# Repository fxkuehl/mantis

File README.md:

# Mantis hex ergo keyboard — Development branch

>

This is the development branch of Mantis. It's taking me way longer than expected to finish version 1.0 for various reasons—including my day job, other hobbies, some pretty ambitious design goals, and having too much fun making the renders look pretty. But I am getting closer to the finish line, so it's a good time to share an update in January 2026.

## What's unchanged since v0.3

>

The basic recipe is still the same:

* Compact unibody keyboard with 40 sculpted hexagonal keys
* Simulated key wells using two layers of PCBs and rotated switches
* 30° hand rotation
* 15° tenting
* Choc switches
* Support for per-key RGB LEDs

## What's new in v1.0

>

These are mostly the features that I wanted v1.0 to have when I started working on it in November 2024:

* Integrated trackball or trackpad
* 3D-printed, fully enclosed case hiding switches
* Gasket mounted structure
* New saddle-shaped key cap profile
* Choc v1 and v2 switch compatibility
* Hot-swap
* Designed for easier assembly
* Support for wireless builds with nice!nano
* Support for wired builds with ProMicro-RP2040
* Support for nice!view display

Only the nice!view display option was a later addition as wireless support became a higher priority for me and I realized that RGB LEDs don't work well with small batteries.

## Details and trade-offs

I figured the trackball would be harder to design for than a cirque trackpad, so I started with the trackball design. Once I got down to the nuts and bolts, these were some of the decisions and trade-offs that emerged:

* Trackball: 34mm, static bearings, PMW3610 sensor
    - ambidextrous
    - placement and sensor angle work best for thumb use
    - low power sensor, suitable for wireless builds
    - unfortunately not supported by QMK, but ZMK also supports wired RP2040 controllers
* Losing two thumb keys to make room for the trackball
* Adding two pinky keys to maintain number of keys, provide more layout flexibility
* Gasket-mounted structure allows 1mm vertical movement before bottoming out
* Four 1mm foam or cork layers for sound dampening
* Enclosed case adds minimal bulk with 2.5mm wall thickness and tight tolerances
    - case adds only about 1.5mm total width and depth compared to v0.3
    - extra pinky keys add another 21.5mm total width
* Low-profile design: 2mm lower than v0.3, including the trackball, 6mm lower excluding trackball
    - counter-sunk screws
    - recessed feet
    - internal recesses in base plate and mezzanine for PCB components and pins
    - thinner PCBs and switch plates (1.2mm)
    - 60° angled sensor mount and opening in case bottom enable low trackball position
* Internal use of VIK connectors/cables/signaling (ready for future version with Cirque trackpad)
    - Custom sensor-board is not mechanically VIK-compatible due to space constraints
    - Using identical 12-pin FFC cables for VIK connection and upper keyboard-PCB connection
* PCB configuration through solder jumpers
    - not enough controller pins to support all VIK features + display + LEDs all at once
    - support for cirque trackpads (without VIK module) requires disconnecting VIK 5V and LED pins
    - power source selection for LEDs depending on the controller
* Intended for automated PCB-assembly
    - no manual SMD soldering required (hand-soldering FFC connectors would be a pain)
    - all SMD components placed on the bottom of the PCBs
    - still requires manual soldering of jumpers and through-hole components
* Easy controller socketing with standard pin-headers
* Battery compartment and connector
    - using common JST-PH 2mm-pitch connector
    - accessible without disassembly other than removing the base plate
    - enough room for 501240, 501235, 401230 or similar LiPo batteries
    - 100-200mAh should be good for several weeks on a charge
* Attempting crude ESD protection with a ferrite bead between ground plane and controller GND pins
    - proper ESD would involve a [Unified Daughterboard](https://unified-daughterboard.github.io/#/) and integrated controller, but I'm not ready to make that jump in v1.0

## What's done

>

Over the last year and 2 months I went through more than 140 revisions on this Git branch to get to this point:

* Closed most open design and fit issues
* Ergogen design of all the PCB, plate and foam outlines and PCB templates
* Parametric OpenSCAD model of the case for gasket-mounted trackball version
* Parametric OpenSCAD models of saddle-shaped key cap profile with Choc v1 and v2 stems
* Main PCB schematic and routing complete

## What's left to do

If I can check off each of the following TODO items in a weekend, I'll have the first working prototype ready by the spring equinox. This estimate is on the optimistic side, given my track record. But if all works without major setbacks, I expect to publish the complete design and a build guide some time this spring.

High-level TODO-list:

* Upper PCB schematic and routing
* Fix-up the sensor board with updated outline and schematic
* Experiment with panelization and V-cuts to make multi-PCB+plate production easier/cheaper
* Create the PCB production files, order PCBs and plates
* Find some local 3D-printing/laser cutting services or maker spaces to make the case and foam/cork layers
* Order all the additional parts
* Build a prototype or two
* Learn ZMK and create the firmware
* Pray that everything fits and works as designed

## What's next

While the gasket-mounted trackball version is meant to be my ideal home or office keyboard, I want to make the perfect on-the-go or travel keyboard next. The PCBs are already designed to support this, so it should only be a matter of a modified case design and parameters as well as a different firmware build:

* Switch plates integrated into the case
    - more sturdy
    - easier assembly
    - slightly lower without the gaskets
* Cirque trackpad
    - biggest size I can fit is probably 35mm
    - mouse buttons integrated into the case
* Low-profile with shallower key-wells
    - tenting angle lowered to 10° (less rise between main and upper PCB/plate)
    - less-tilted key caps
    - aiming for about 25-26mm total height

>

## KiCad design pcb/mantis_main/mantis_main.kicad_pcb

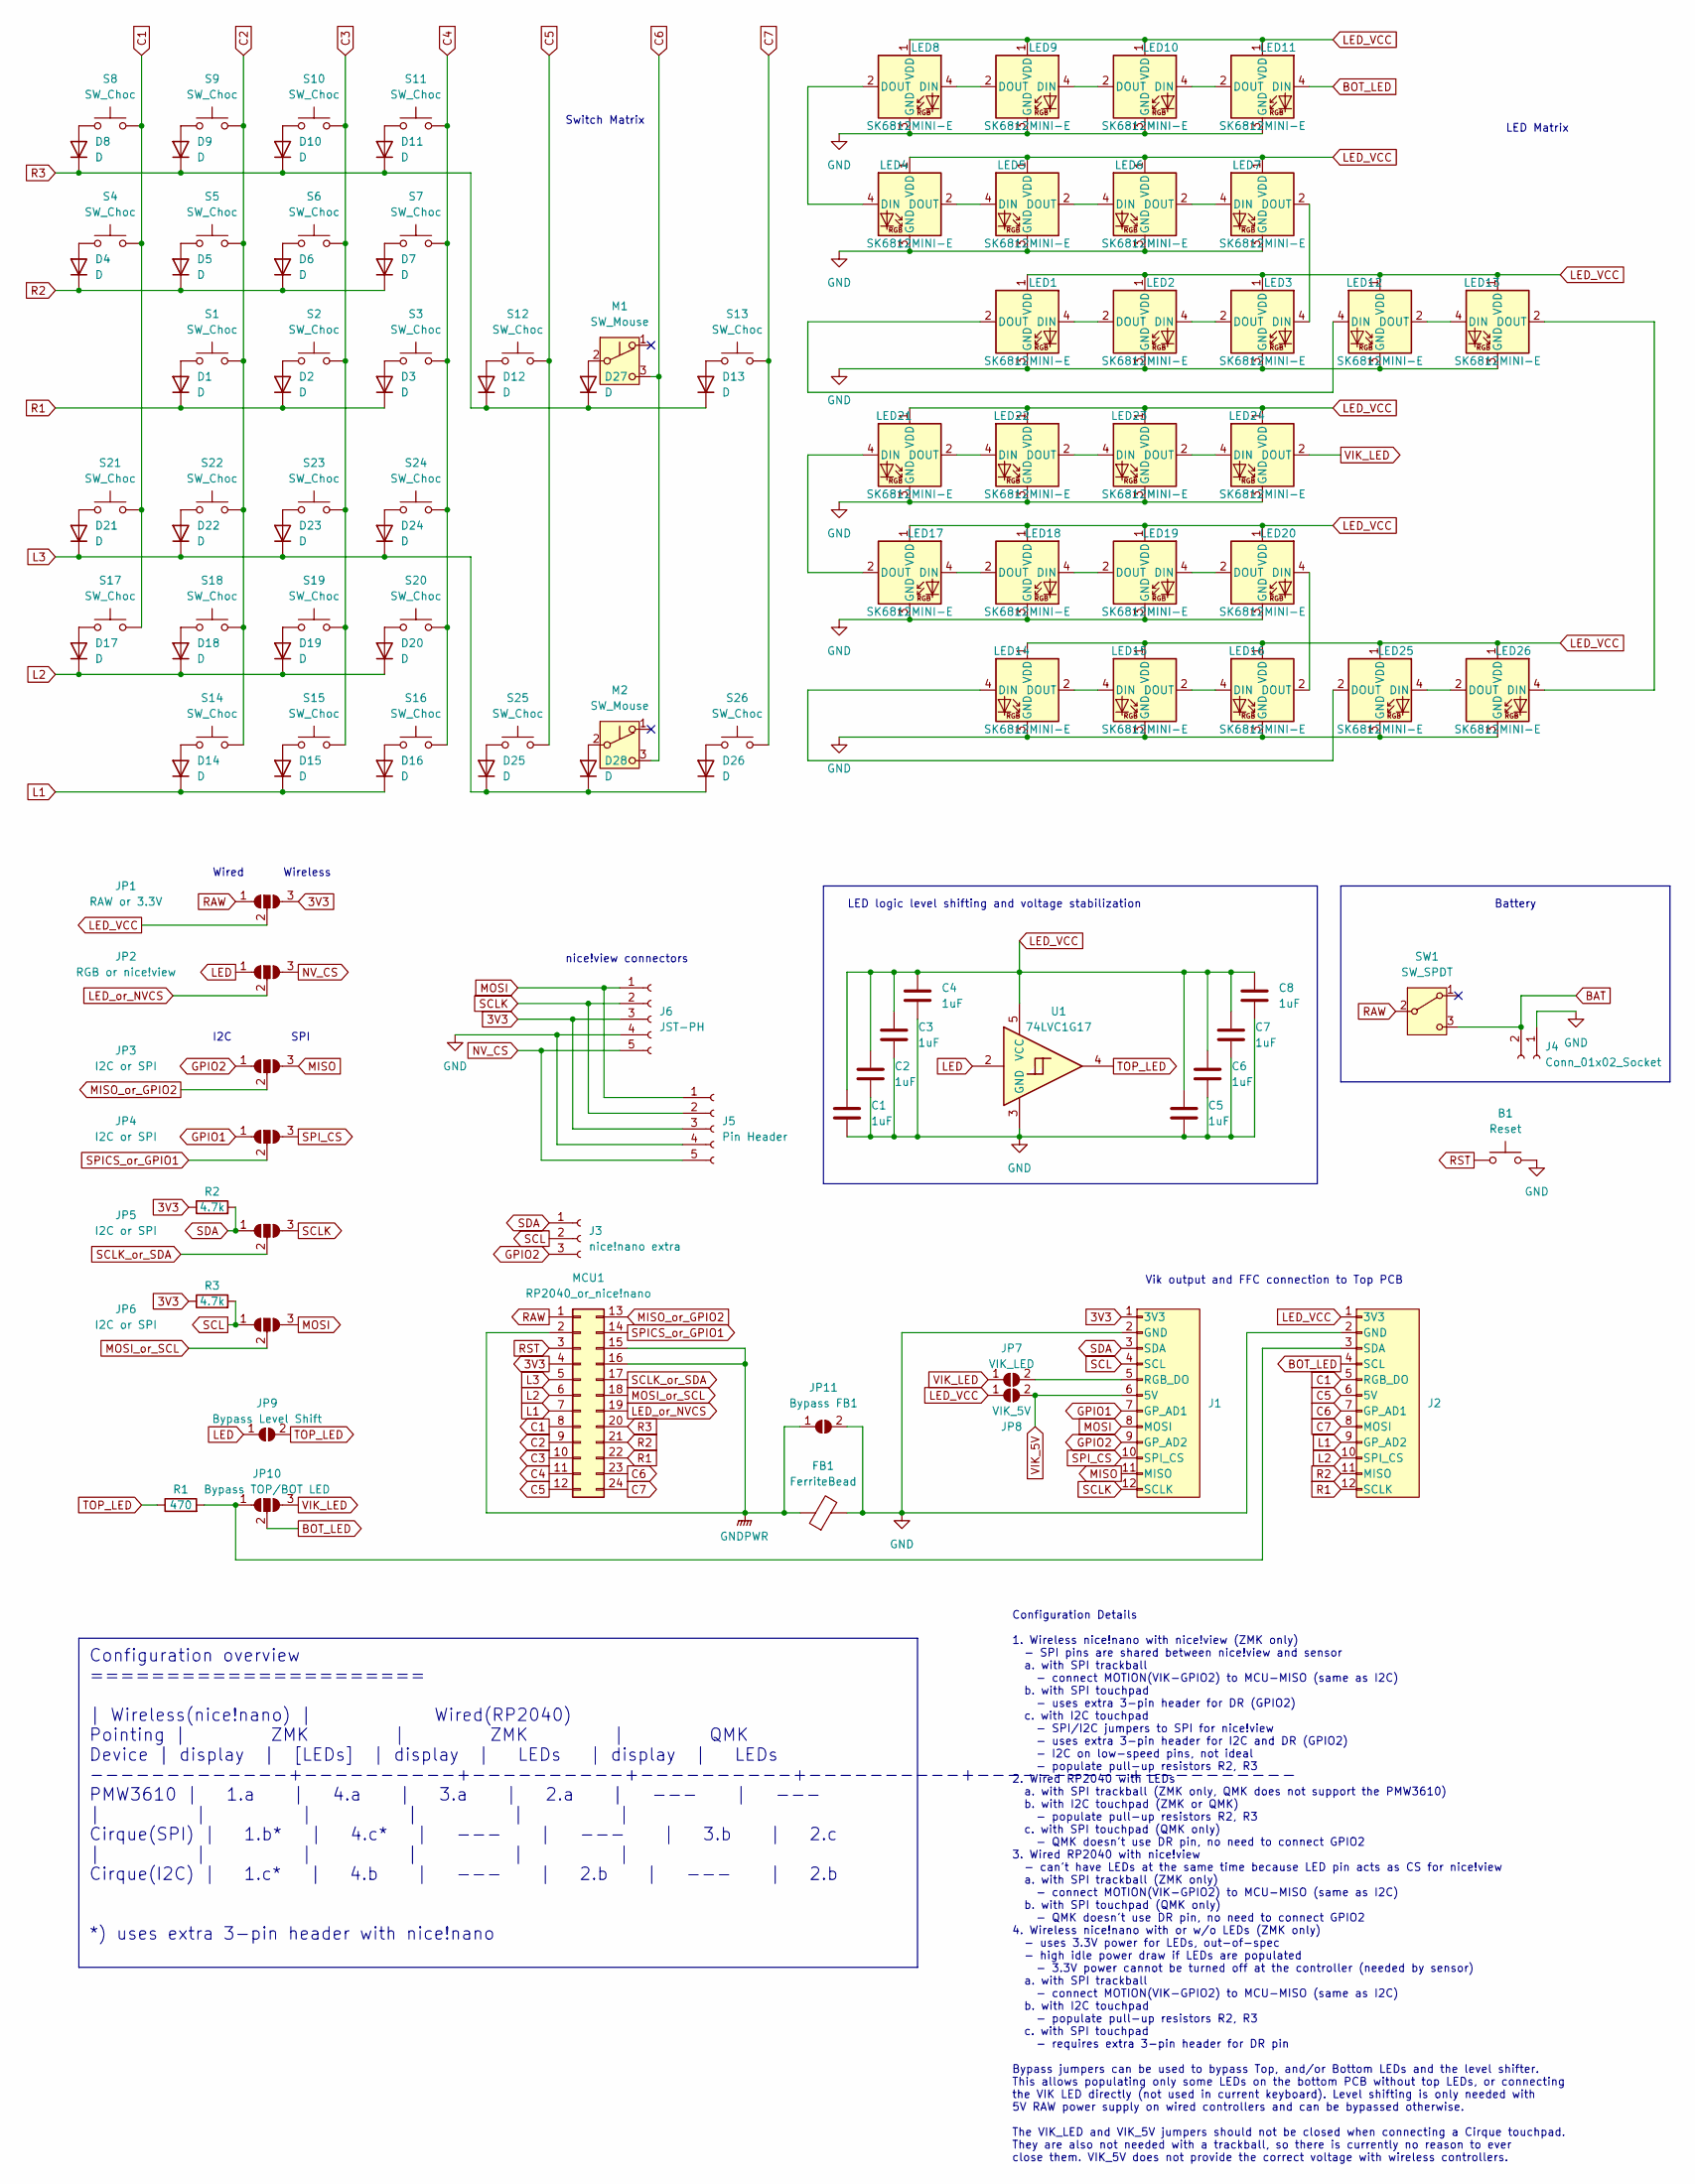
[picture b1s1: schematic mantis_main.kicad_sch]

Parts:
B1: Reset; SW_SPST_SKQG_WithoutStem
C1, C2, C3, C4, C5, C6, C7, C8: 1uF; C_0603_1608Metric
D1, D2, D3, D4, D5, D6, D7, D8, D9, D10, D11, D12, D13, D14, D15, D16, D17, D18, D19, D20, D21, D22, D23, D24, D25, D26, D27, D28: D; D_SOD-123
FB1: FerriteBead; C_0805_2012Metric
J1, J2: vik-keyboard-connector-horizontal
J3: nice!nano extra; PinSocket_1x03_P2.54mm_Vertical
J4: Conn_01x02_Socket; JST_PH_S2B-PH-K_1x02_P2.00mm_Horizontal
J5: Pin Header; PinSocket_1x05_P2.54mm_Vertical
J6: JST-PH; JST_PH_S5B-PH-K_1x05_P2.00mm_Horizontal
JP1: RAW or 3.3V; SolderJumper-3_P1.3mm_Open_RoundedPad1.0x1.5mm
JP2: RGB or nice!view; SolderJumper-3_P1.3mm_Open_RoundedPad1.0x1.5mm
JP3, JP4, JP5, JP6: I2C or SPI; SolderJumper-3_P1.3mm_Open_RoundedPad1.0x1.5mm
JP7: VIK_LED; SolderJumper-2_P1.3mm_Open_RoundedPad1.0x1.5mm
JP8: VIK_5V; SolderJumper-2_P1.3mm_Open_RoundedPad1.0x1.5mm
JP9: Bypass Level Shift; SolderJumper-2_P1.3mm_Open_RoundedPad1.0x1.5mm
JP10: Bypass TOP/BOT LED; SolderJumper-3_P1.3mm_Open_RoundedPad1.0x1.5mm
JP11: Bypass FB1; SolderJumper-2_P1.3mm_Open_RoundedPad1.0x1.5mm
LED1, LED2, LED3, LED4, LED5, LED6, LED7, LED8, LED9, LED10, LED11, LED12, LED13, LED14, LED15, LED16, LED17, LED18, LED19, LED20, LED21, LED22, LED23, LED24, LED25, LED26: SK6812MINI-E; SK6812_MINI-E-back
M1, M2: SW_Mouse; D2F
MCU1: RP2040_or_nice!nano; ProMicro-back
R1: 470; R_0603_1608Metric
R2, R3: 4.7k; R_0603_1608Metric
S1, S2, S3, S4, S5, S6, S7, S8, S9, S10, S11, S12, S13, S14, S15, S16, S17, S18, S19, S20, S21, S22, S23, S24, S25, S26: SW_Choc; PG1350-hotswap
SW1: SW_SPDT; SW_SPDT_PCM12
U1: 74LVC1G17; SOT-353_SC-70-5

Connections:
3V3: J1.1 (3V3), J5.3, J6.3, JP1.3 (B), MCU1.4, R2.1, R3.1
BAT: J4.2, SW1.3 (C)
BOT_LED: J2.4 (SCL), JP10.2 (C), LED11.4 (DIN)
C1: J2.5 (RGB_DO), MCU1.8, S4.2, S8.2, S17.2, S21.2
C2: MCU1.9, S1.2, S5.2, S9.2, S14.2, S18.2, S22.2
C3: MCU1.10, S2.2, S6.2, S10.2, S15.2, S19.2, S23.2
C4: MCU1.11, S3.2, S7.2, S11.2, S16.2, S20.2, S24.2
C5: J2.6 (5V), MCU1.12, S12.2, S25.2
C6: J2.7 (GP_AD1), M1.3 (C), M2.3 (C), MCU1.23
C7: J2.8 (MOSI), MCU1.24, S13.2, S26.2
GND: B1.2, C1.2, C2.2, C3.2, C4.2, C5.2, C6.2, C7.2, C8.2, FB1.2, J1.2 (GND), J2.2 (GND), J4.1, J5.4, J6.4, JP11.2 (B), LED1.3 (GND), LED2.3 (GND), LED3.3 (GND), LED4.3 (GND), LED5.3 (GND), LED6.3 (GND), LED7.3 (GND), LED8.3 (GND), LED9.3 (GND), LED10.3 (GND), LED11.3 (GND), LED12.3 (GND), LED13.3 (GND), LED14.3 (GND), LED15.3 (GND), LED16.3 (GND), LED17.3 (GND), LED18.3 (GND), LED19.3 (GND), LED20.3 (GND), LED21.3 (GND), LED22.3 (GND), LED23.3 (GND), LED24.3 (GND), LED25.3 (GND), LED26.3 (GND), U1.3 (GND)
GNDPWR: FB1.1, JP11.1 (A), MCU1.2, MCU1.15, MCU1.16
GPIO1: J1.7 (GP_AD1), JP4.1 (A)
GPIO2: J1.9 (GP_AD2), J3.3, JP3.1 (A)
L1: D14.1 (K), D15.1 (K), D16.1 (K), J2.9 (GP_AD2), MCU1.7
L2: D17.1 (K), D18.1 (K), D19.1 (K), D20.1 (K), J2.10 (SPI_CS), MCU1.6
L3: D21.1 (K), D22.1 (K), D23.1 (K), D24.1 (K), D25.1 (K), D26.1 (K), D28.1 (K), MCU1.5
LED: JP2.1 (A), JP9.1 (A), U1.2
LED_VCC: C1.1, C2.1, C3.1, C4.1, C5.1, C6.1, C7.1, C8.1, J2.1 (3V3), JP1.2 (C), JP8.1 (A), LED1.1 (VDD), LED2.1 (VDD), LED3.1 (VDD), LED4.1 (VDD), LED5.1 (VDD), LED6.1 (VDD), LED7.1 (VDD), LED8.1 (VDD), LED9.1 (VDD), LED10.1 (VDD), LED11.1 (VDD), LED12.1 (VDD), LED13.1 (VDD), LED14.1 (VDD), LED15.1 (VDD), LED16.1 (VDD), LED17.1 (VDD), LED18.1 (VDD), LED19.1 (VDD), LED20.1 (VDD), LED21.1 (VDD), LED22.1 (VDD), LED23.1 (VDD), LED24.1 (VDD), LED25.1 (VDD), LED26.1 (VDD), U1.5 (VCC)
LED_or_NVCS: JP2.2 (C), MCU1.19
MISO: J1.11 (MISO), JP3.3 (B)
MISO_or_GPIO2: JP3.2 (C), MCU1.13
MOSI: J1.8 (MOSI), J5.1, J6.1, JP6.3 (B)
MOSI_or_SCL: JP6.2 (C), MCU1.18
NV_CS: J5.5, J6.5, JP2.3 (B)
unnamed: D1.2 (A), S1.1
unnamed: D2.2 (A), S2.1
unnamed: D3.2 (A), S3.1
unnamed: D4.2 (A), S4.1
unnamed: D5.2 (A), S5.1
unnamed: D6.2 (A), S6.1
unnamed: D7.2 (A), S7.1
unnamed: D8.2 (A), S8.1
unnamed: D9.2 (A), S9.1
unnamed: D10.2 (A), S10.1
unnamed: D11.2 (A), S11.1
unnamed: D12.2 (A), S12.1
unnamed: D13.2 (A), S13.1
unnamed: D14.2 (A), S14.1
unnamed: D15.2 (A), S15.1
unnamed: D16.2 (A), S16.1
unnamed: D17.2 (A), S17.1
unnamed: D18.2 (A), S18.1
unnamed: D19.2 (A), S19.1
unnamed: D20.2 (A), S20.1
unnamed: D21.2 (A), S21.1
unnamed: D22.2 (A), S22.1
unnamed: D23.2 (A), S23.1
unnamed: D24.2 (A), S24.1
unnamed: D25.2 (A), S25.1
unnamed: D26.2 (A), S26.1
unnamed: D27.2 (A), M1.2 (B)
unnamed: D28.2 (A), M2.2 (B)
unnamed: J1.5 (RGB_DO), JP7.2 (B)
unnamed: J2.3 (SDA), JP10.1 (A), R1.2
unnamed: LED1.4 (DIN), LED2.2 (DOUT)
unnamed: LED1.2 (DOUT), LED12.4 (DIN)
unnamed: LED2.4 (DIN), LED3.2 (DOUT)
unnamed: LED3.4 (DIN), LED7.2 (DOUT)
unnamed: LED4.4 (DIN), LED8.2 (DOUT)
unnamed: LED4.2 (DOUT), LED5.4 (DIN)
unnamed: LED5.2 (DOUT), LED6.4 (DIN)
unnamed: LED6.2 (DOUT), LED7.4 (DIN)
unnamed: LED8.4 (DIN), LED9.2 (DOUT)
unnamed: LED10.4 (DIN), LED11.2 (DOUT)
unnamed: LED9.4 (DIN), LED10.2 (DOUT)
unnamed: LED12.2 (DOUT), LED13.4 (DIN)
unnamed: LED13.2 (DOUT), LED26.4 (DIN)
unnamed: LED14.4 (DIN), LED25.2 (DOUT)
unnamed: LED14.2 (DOUT), LED15.4 (DIN)
unnamed: LED15.2 (DOUT), LED16.4 (DIN)
unnamed: LED16.2 (DOUT), LED20.4 (DIN)
unnamed: LED17.4 (DIN), LED18.2 (DOUT)
unnamed: LED17.2 (DOUT), LED21.4 (DIN)
unnamed: LED18.4 (DIN), LED19.2 (DOUT)
unnamed: LED19.4 (DIN), LED20.2 (DOUT)
unnamed: LED21.2 (DOUT), LED22.4 (DIN)
unnamed: LED22.2 (DOUT), LED23.4 (DIN)
unnamed: LED23.2 (DOUT), LED24.4 (DIN)
unnamed: LED25.4 (DIN), LED26.2 (DOUT)
R1: D1.1 (K), D2.1 (K), D3.1 (K), J2.12 (SCLK), MCU1.22
R2: D4.1 (K), D5.1 (K), D6.1 (K), D7.1 (K), J2.11 (MISO), MCU1.21
R3: D8.1 (K), D9.1 (K), D10.1 (K), D11.1 (K), D12.1 (K), D13.1 (K), D27.1 (K), MCU1.20
RAW: JP1.1 (A), MCU1.1, SW1.2 (B)
RST: B1.1, MCU1.3
SCL: J1.4 (SCL), J3.2, JP6.1 (A), R3.2
SCLK: J1.12 (SCLK), J5.2, J6.2, JP5.3 (B)
SCLK_or_SDA: JP5.2 (C), MCU1.17
SDA: J1.3 (SDA), J3.1, JP5.1 (A), R2.2
SPICS_or_GPIO1: JP4.2 (C), MCU1.14
SPI_CS: J1.10 (SPI_CS), JP4.3 (B)
TOP_LED: JP9.2 (B), R1.1, U1.4
VIK_5V: J1.6 (5V), JP8.2 (B)
VIK_LED: JP7.1 (A), JP10.3 (B), LED24.2 (DOUT)

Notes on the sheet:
Configuration overview ====================== | Wireless(nice!nano) | Wired(RP2040) Pointing | ZMK | ZMK | QMK Device | display | [LEDs] | display | LEDs | display | LEDs -------------+----------+----------+----------+----------+----------+---------- PMW3610 | 1.a | 4.a | 3.a | 2.a | --- | --- | | 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
Wired
Battery
LED Matrix
nice!view connectors
SPI
Wireless
LED logic level shifting and voltage stabilization
Configuration Details 1. Wireless nice!nano with nice!view (ZMK only) - SPI pins are shared between nice!view and sensor a. with SPI trackball - connect MOTION(VIK-GPIO2) to MCU-MISO (same as I2C) b. with SPI touchpad - uses extra 3-pin header for DR (GPIO2) c. with I2C touchpad - SPI/I2C jumpers t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
Switch Matrix
I2C
Vik output and FFC connection to Top PCB

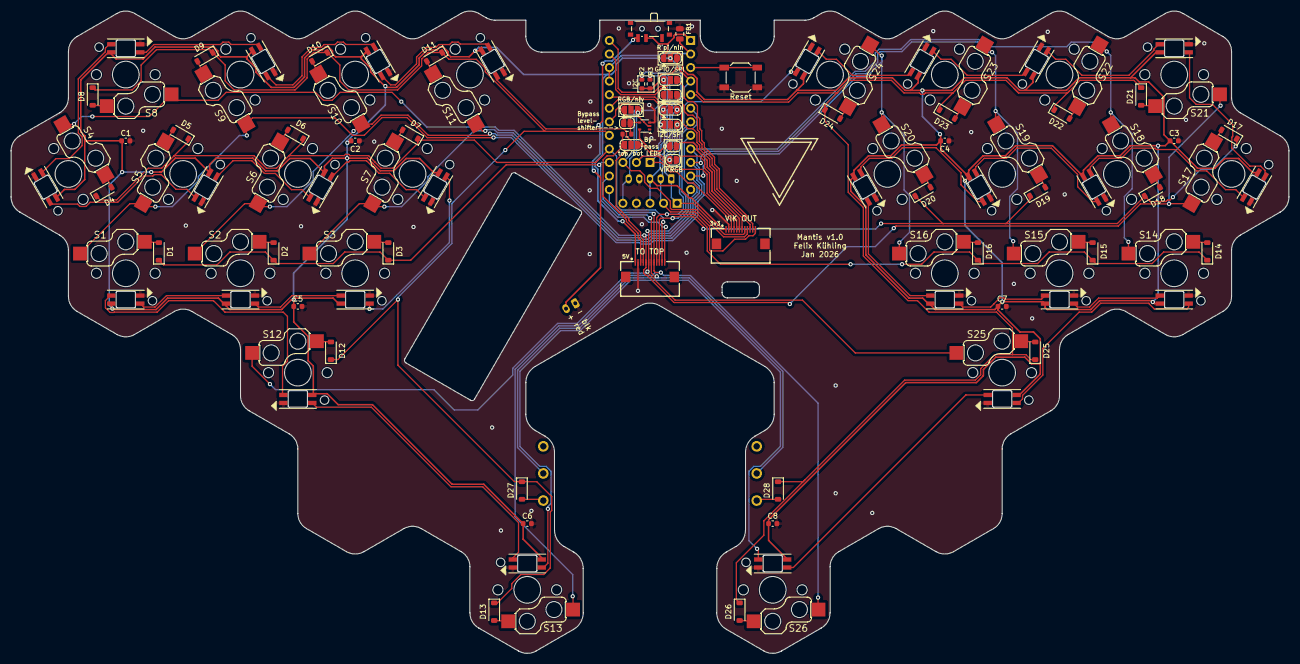
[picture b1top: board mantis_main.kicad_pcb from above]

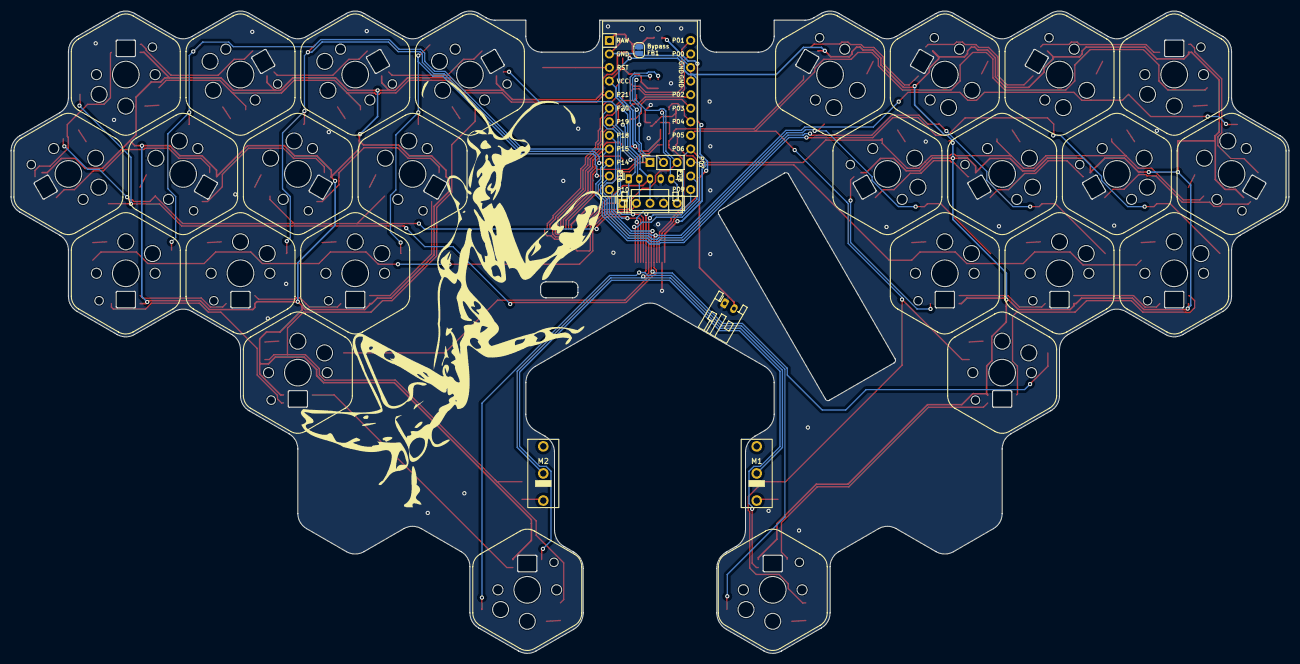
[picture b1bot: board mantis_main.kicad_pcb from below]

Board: 2 copper layers, 239.5 x 120.4 mm, 115 parts (7 on the bottom side), 94 nets.

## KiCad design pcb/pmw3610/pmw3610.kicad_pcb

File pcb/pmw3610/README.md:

# PMW3610 trackball pcb - Mantis Version

## Overview

This module is based on the
[PMW3610 XS module](https://github.com/sadekbaroudi/vik/tree/master/pcb/pmw3610-xs)
by Sadek Baroudi. The schematic is identical. The components are rearranged
to fit my PCB outline. The PMW3610 footprint is modified to make the cutout
slightly smaller, which leaves a bit more PCB material and a wider ground
zone above the sensor. All breakout pins are present but some labels didn't
fit on the back side.

The VIK module certification below is updated to reflect the non-standard
form factor. This module is meant to fit the Mantis v1.0 keyboard and
should be attached to the VIK OUT port of the main PCB with an FFC type A
cable.

## Original notes by Sadek Baroudi

First and foremost, note that this module is identical to the PMW3610 module, except in a extra small (xs) form factor.

This is a VIK module to use a PMW3610 motion sensor. This sensor is primarily used for mousing applications.

The most common use in the keyboard community is for trackballs.

Note that while I2C, RGB, and extra GPIO are broken out, but are not used in the circuitry, so they are not needed for the sensor. There are also footprints for I2C pull up resistors, which are also not needed, as I2C is not used.

There is a jumper for NRESET, with an option to:  
* Route to 3.3V, which means that it's inactive
* Route to the VIK GPIO 1, which allows you to control the state with the connected controller

You do not need to solder the jumper at all, since there is a weak pull up resistor in the PMW3610, but if you have any trouble with the state, and want to explicitly attach to 3.3V, you can.

## IMPORTANT

The PMW3610 sensor is a low power sensor, and uses serial data communication with a motion status pin (to reduce power consumption). This pcb uses the SPI pins, but is not standard SPI communication. This means that you cannot connect this module to a controller or board that uses the VIK SPI pins for any other purpose. These are being treated as standard GPIO for this module. This is not a VIK compliant module!

That said, if you understand the above, you can still use this module with no issues.

## Alternate parts

The LDO seems to be frequently out of stock at JLCPCB. The part number specified in this module is `C146366`. As an alternate part, you can try to use `C2862411` or `C2869109` (`TLV70019DDCR` or `TLV70019DDCT`, respectively)

## Fabrication and BOM

For PCB fabrication, you can use the files in the production folder.

* gerbers.zip - the file used to fabricate the pcb
* bom.csv - used for PCBA. You can also use the part numbers in this file to look up the exact parts as [lcsc.com](https://lcsc.com)
* positions.csv - used for PCBA

Using the 3 files above, this has been tested at [jlcpcb.com](https://jlcpcb.com)

## VIK module certification

| Category                | Classification          | Response           |
| ----------------------- | ----------------------- | ------------------ |
| FPC connector           | Required                | :heavy_check_mark: |
| Breakout pins           | Recommended             | :heavy_check_mark: |
| Uses: SPI               | Optional                | :heavy_check_mark: |
| SPI used for SPI only   | Strongly recommended    | :x:                |
| Uses: I2C               | Optional                | :x:                |
| I2C used for I2C only   | Strongly Recommended    | :x:                |
| I2C pull ups            | Required                | N/A                |
| Uses: RGB               | Optional                | :x:                |
| Uses: Extra GPIO 1      | Optional                | :x:                |
| Uses: Extra GPIO 2      | Optional                | :x:                |
| Standard PCB Size/Mount | Strongly recommended    | :x:                |

## PCB images

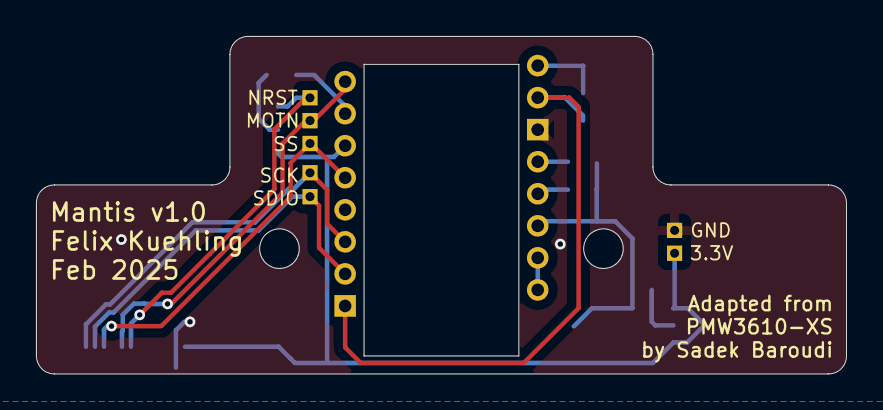
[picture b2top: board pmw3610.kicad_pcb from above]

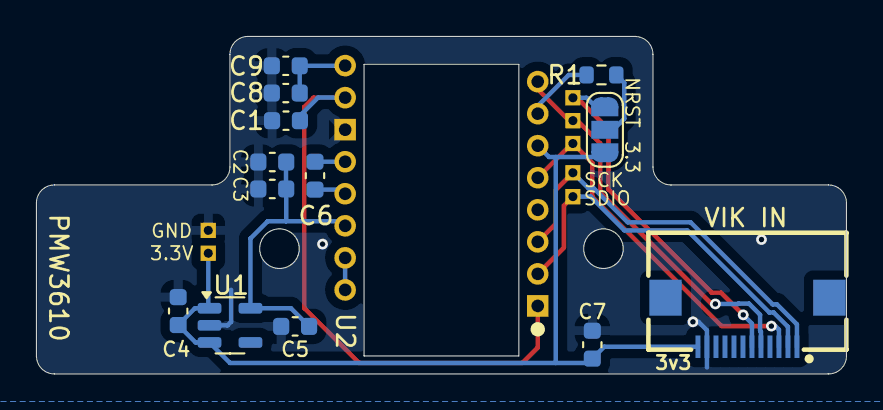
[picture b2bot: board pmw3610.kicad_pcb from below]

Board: 2 copper layers, 45.0 x 18.8 mm, 21 parts (14 on the bottom side), 15 nets.

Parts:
C1, C2, C3, C6, C7, C8, C9: 4.7uF; C_0603_1608Metric
C4: 0.1u; C_0603_1608Metric
C5: 1u; C_0603_1608Metric
J1, J2, J3, J5, J6, J7, J8: Conn_01x01_Socket; PinHeader_1x01_P1.00mm_NoSilk
J4: vik-module-connector-horizontal
JP1: SolderJumper_3_Open; SolderJumper-3_P1.3mm_Open_RoundedPad1.0x1.5mm_NumberLabels
R1: 2M; R_0603_1608Metric
U1: TCR2EF19; SOT-23-5
U2: PMW3610

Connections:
GND: C1.2, C2.2, C3.2, C4.1, C5.2, C7.2, C8.2, C9.2, J1.1, J4.11 (GND), U1.2 (GND), U2.11 (GND)
MOTION: J4.5 (MOSI), J5.1, U2.8 (MOTION)
NCS: J4.3 (SPI_CS), J6.1, U2.5 (NCS)
NRESET: J4.6 (GP_AD1), J8.1, JP1.1 (A)
unnamed: JP1.2 (C), R1.2
unnamed: C1.1, U2.1 (+VCSEL), U2.10 (PASS_T)
unnamed: U2.15 (XYLASER), U2.16 (-VCSEL)
unnamed: C6.1, U2.13 (CN)
unnamed: C6.2, U2.12 (CP)
unnamed: R1.1, U2.7 (NRESET)
unnamed: C8.1, C9.1, U2.9 (VCP)
SCLK: J3.1, J4.1 (SCLK), U2.3 (SCLK)
SDIO: J2.1, J4.2 (MISO), U2.2 (SDIO)
VDD_1V9: C2.1, C3.1, C5.1, U1.5 (OUT), U2.14 (VDD)
VDD_3.3V: C4.2, C7.1, J4.12 (3V3), J7.1, JP1.3 (B), U1.1 (IN), U1.3 (EN), U2.6 (VDDIO)

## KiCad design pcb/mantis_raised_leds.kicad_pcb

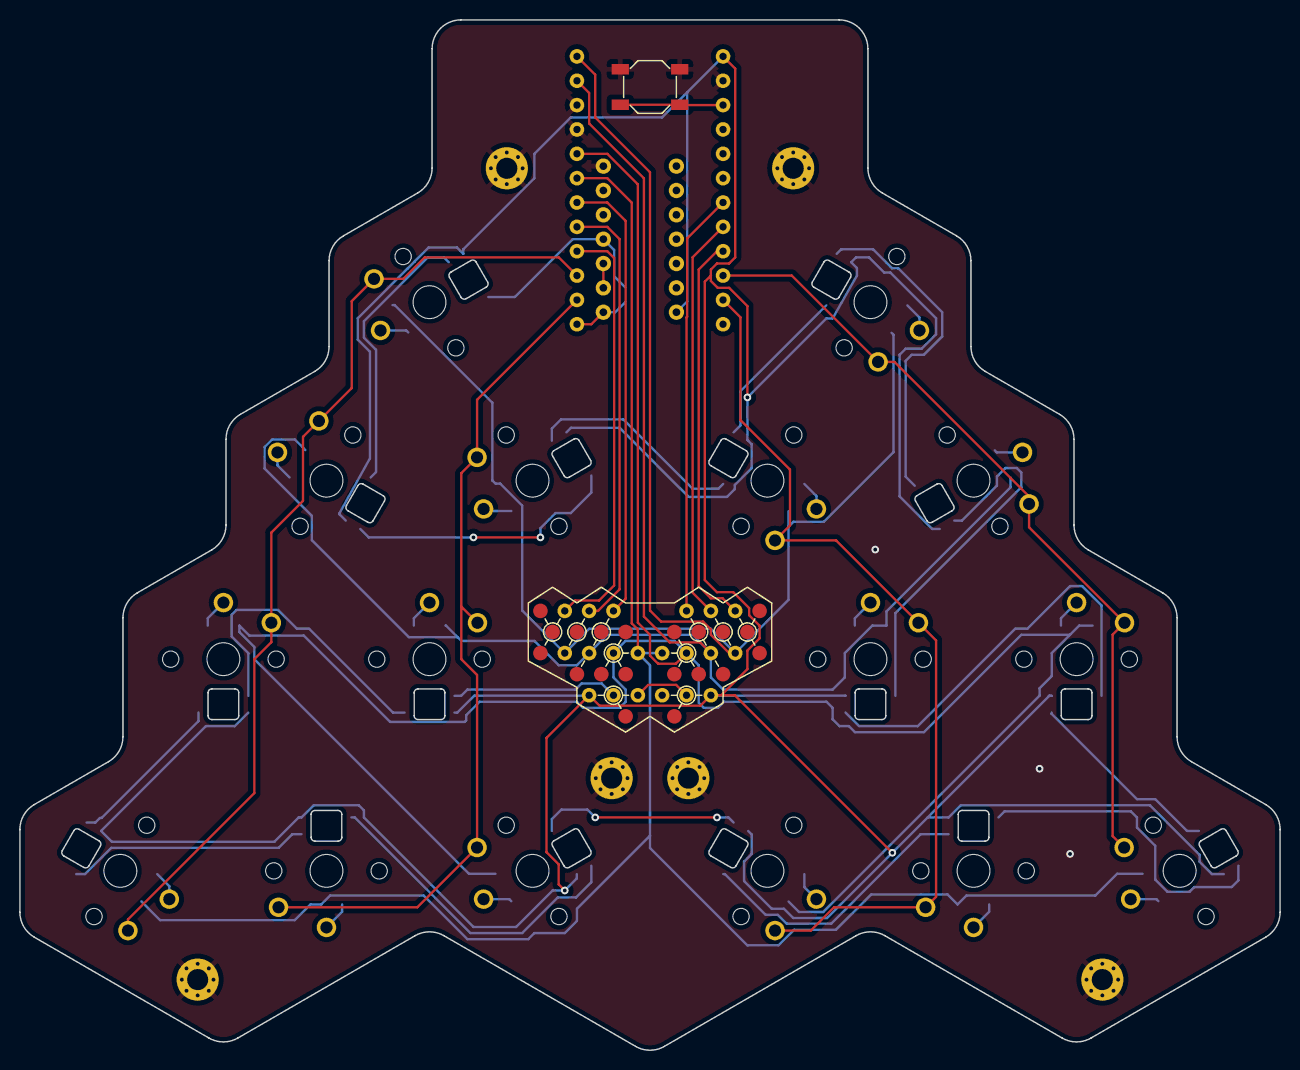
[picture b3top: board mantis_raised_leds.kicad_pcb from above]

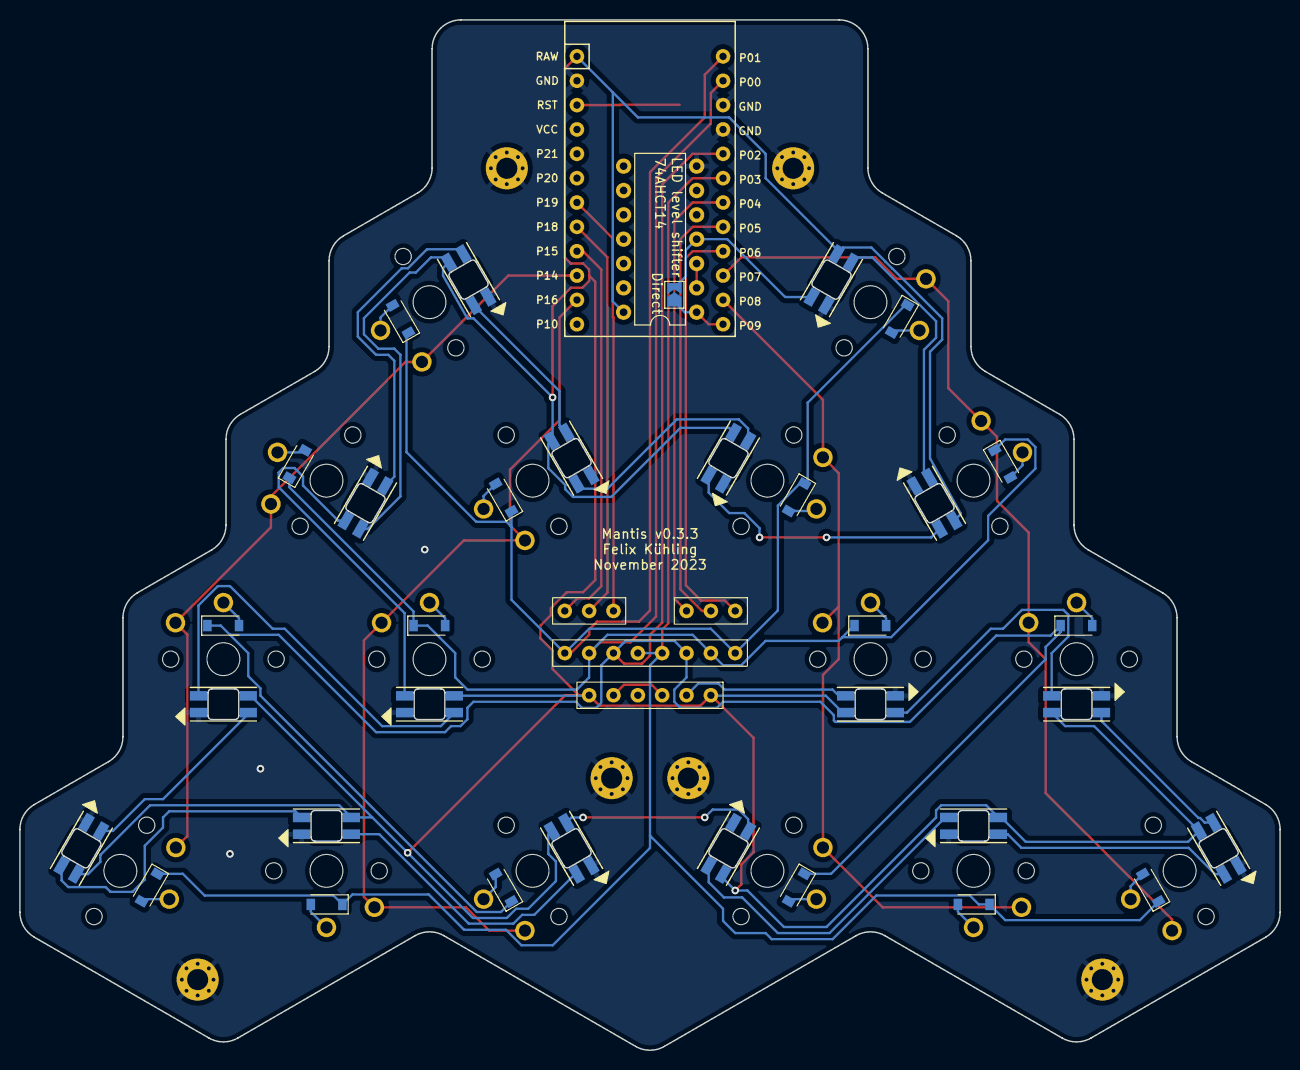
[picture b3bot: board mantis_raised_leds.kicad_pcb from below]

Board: 2 copper layers, 131.5 x 107.5 mm, 59 parts (2 on the bottom side), 52 nets.

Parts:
B1: SW_TACT_ALPS_SKQGABE010
D1, D2, D3, D4, D5, D6, D7, D8, D9, D10, D11, D12, D13, D14, D15, D16: SOD123-back
Direct: SolderJumper-2_P1.3mm_Open_TrianglePad1.0x1.5mm
LED1, LED2, LED3, LED4, LED5, LED6, LED7, LED8, LED9, LED10, LED11, LED12, LED13, LED14, LED15, LED16: SK6812_MINI-E-back
LED level shifter: DIP-14_W7.62mm
MCU1: ProMicro-back
MCU2: Connector-20pin
PAD1, PAD2, PAD3, PAD4, PAD5, PAD6: MountingHole_2.2mm_M2_Pad_Via
S1, S2, S3, S4, S5, S6, S7, S8, S9, S10, S11, S12, S13, S14, S15, S16: PG1350

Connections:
C1: MCU1.19, MCU2.19
C2: MCU1.20, MCU2.20
C3: MCU1.21, MCU2.21
C4: MCU1.22, S1.1, S3.1, S5.1, S7.1
C5: MCU1.23, S2.1, S4.1, S6.1, S8.1
GND: B1.1, LED1.3, LED2.3, LED3.3, LED4.3, LED5.3, LED6.3, LED7.3, LED8.3, LED9.3, LED10.3, LED11.3, LED12.3, LED13.3, LED14.3, LED15.3, LED16.3, LED level shifter.7, MCU1.2, MCU1.15, MCU1.16, PAD1.1, PAD2.1, PAD3.1, PAD4.1, PAD5.1, PAD6.1
LED: Direct.1, LED level shifter.1, MCU1.24
M_C1: MCU1.7, MCU2.7
M_C2: MCU1.8, MCU2.8
M_C3: MCU1.9, MCU2.9
M_C4: MCU1.10, S9.1, S11.1, S13.1, S15.1
M_C5: MCU1.11, S10.1, S12.1, S14.1, S16.1
R1: D5.1, D6.1, D13.1, D14.1, MCU1.17, MCU2.10, MCU2.17
R2: D3.1, D4.1, D11.1, D12.1, MCU1.14, MCU2.6, MCU2.14
R3: D1.1, D2.1, D9.1, D10.1, MCU1.13, MCU2.5, MCU2.13
RST: B1.2, MCU1.3
RT: D7.1, D8.1, D15.1, D16.1, MCU1.18, MCU2.11, MCU2.18
VCC: LED1.1, LED2.1, LED3.1, LED4.1, LED5.1, LED6.1, LED7.1, LED8.1, LED9.1, LED10.1, LED11.1, LED12.1, LED13.1, LED14.1, LED15.1, LED16.1, LED level shifter.14, MCU1.1, MCU2.4, MCU2.22
c4_r1: D5.2, S5.2
c4_r2: D3.2, S3.2
c4_r3: D1.2, S1.2
c4_rt: D7.2, S7.2
c5_r1: D6.2, S6.2
c5_r2: D4.2, S4.2
c5_r3: D2.2, S2.2
c5_rt: D8.2, S8.2
di_c4_r1: LED5.4, LED7.2
di_c4_r2: LED1.2, LED3.4
di_c4_r3: Direct.2, LED1.4, LED level shifter.4
di_c4_rt: LED7.4, LED8.2
di_c5_r1: LED6.4, LED14.2
di_c5_r2: LED4.4, LED5.2
di_c5_r3: LED2.4, LED3.2
di_c5_rt: LED6.2, LED8.4
di_mirror_c3_r3: MCU2.12, MCU2.24
di_mirror_c4_r1: LED12.2, LED13.4
di_mirror_c4_r2: LED9.2, LED11.4
di_mirror_c4_r3: LED9.4, LED10.2
di_mirror_c4_rt: LED13.2, LED15.4
di_mirror_c5_r1: LED14.4, LED16.2
di_mirror_c5_r2: LED11.2, LED12.4
di_mirror_c5_r3: LED2.2, LED10.4
di_mirror_c5_rt: LED15.2, LED16.4
do_c5_r2: LED4.2, MCU2.23
mirror_c4_r1: D13.2, S13.2
mirror_c4_r2: D11.2, S11.2
mirror_c4_r3: D9.2, S9.2
mirror_c4_rt: D15.2, S15.2
mirror_c5_r1: D14.2, S14.2
mirror_c5_r2: D12.2, S12.2
mirror_c5_r3: D10.2, S10.2
mirror_c5_rt: D16.2, S16.2

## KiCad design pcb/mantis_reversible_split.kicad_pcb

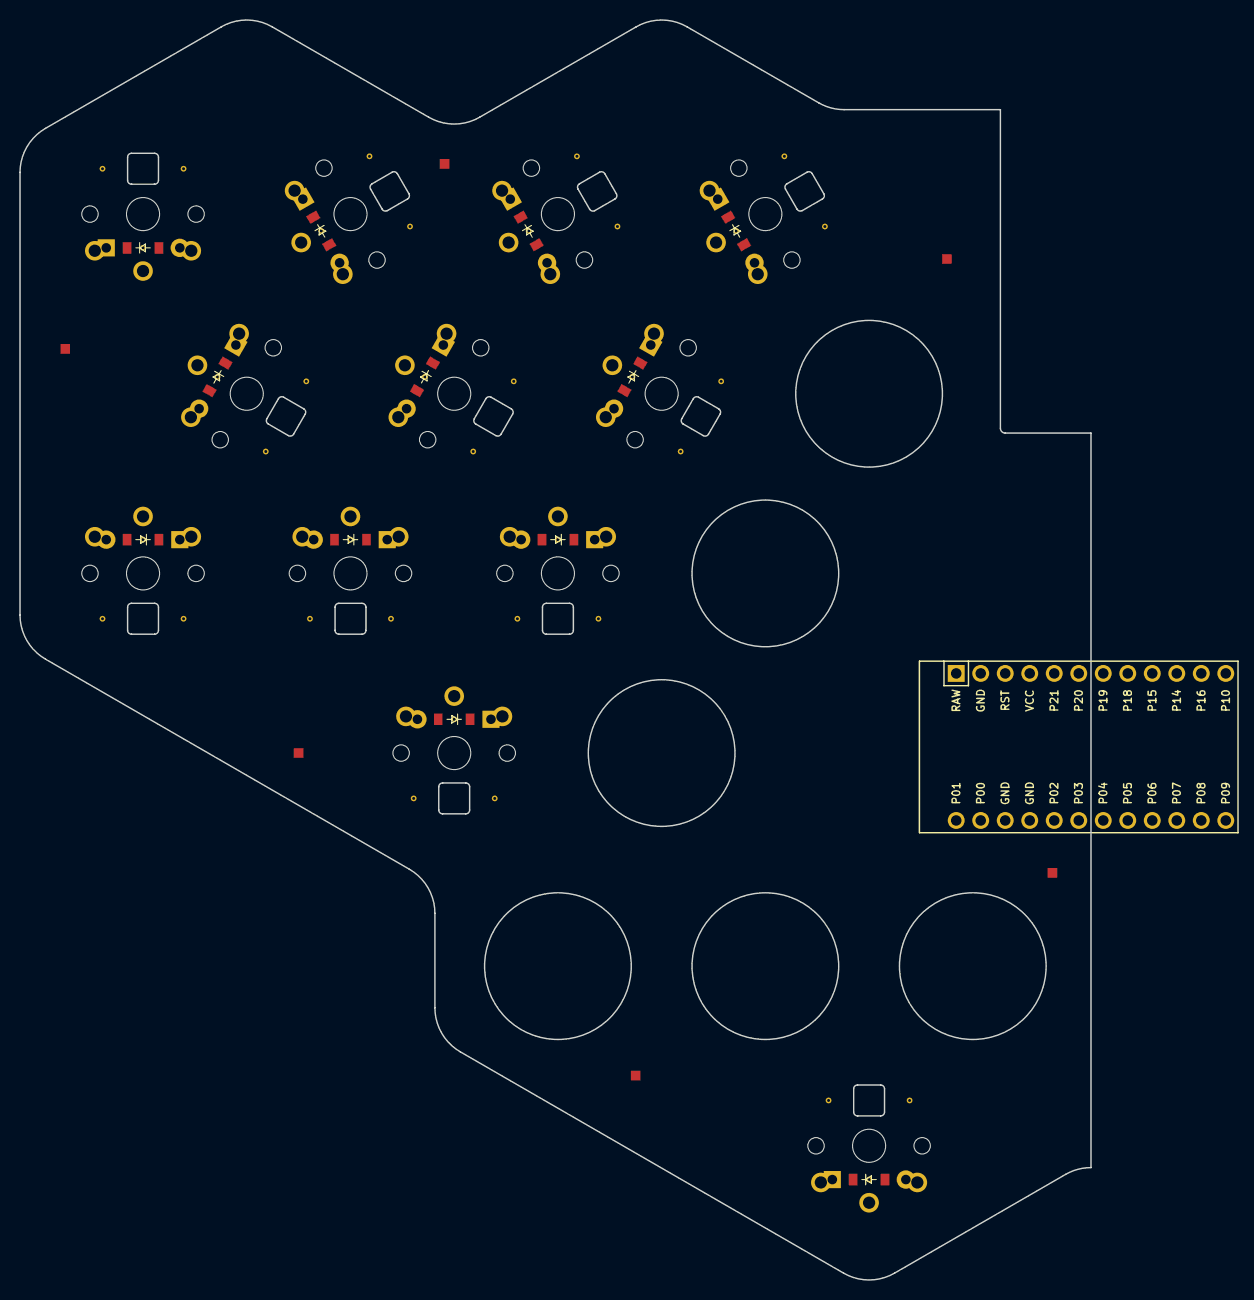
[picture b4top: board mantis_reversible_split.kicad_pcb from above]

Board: 2 copper layers, 111.0 x 130.6 mm, 43 parts (0 on the bottom side), 45 nets, no tracks yet.

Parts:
D1, D2, D3, D4, D5, D6, D7, D8, D9, D10, D11, D12: ComboDiode
LED1, LED2, LED3, LED4, LED5, LED6, LED7, LED8, LED9, LED10, LED11, LED12: WS2812B
MCU1: ProMicro
PAD1, PAD2, PAD3, PAD4, PAD5, PAD6: SMDPad
S1, S2, S3, S4, S5, S6, S7, S8, S9, S10, S11, S12: PG1350

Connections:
C1: MCU1.19, S1.1, S4.1, S7.1, S10.1
C2: MCU1.20, S2.1, S5.1, S8.1, S11.1
C3: MCU1.21, S3.1, S6.1, S9.1, S12.1
GND: LED1.3, LED1.33, LED2.3, LED2.33, LED3.3, LED3.33, LED4.3, LED4.33, LED5.3, LED5.33, LED6.3, LED6.33, LED7.3, LED7.33, LED8.3, LED8.33, LED9.3, LED9.33, LED10.3, LED10.33, LED11.3, LED11.33, LED12.3, LED12.33, MCU1.2, MCU1.15, MCU1.16, PAD1.1, PAD2.1, PAD3.1, PAD4.1, PAD5.1, PAD6.1
R1: D7.1, D8.1, D9.1, MCU1.17
R2: D4.1, D5.1, D6.1, MCU1.14
R3: D1.1, D2.1, D3.1, MCU1.13
RT: D10.1, D11.1, D12.1, MCU1.18
VCC: LED1.1, LED1.11, LED2.1, LED2.11, LED3.1, LED3.11, LED4.1, LED4.11, LED5.1, LED5.11, LED6.1, LED6.11, LED7.1, LED7.11, LED8.1, LED8.11, LED9.1, LED9.11, LED10.1, LED10.11, LED11.1, LED11.11, LED12.1, LED12.11, MCU1.4, MCU1.22
c1_r1: D7.2, S7.2
c1_r2: D4.2, S4.2
c1_r3: D1.2, S1.2
c1_rt: D10.2, S10.2
c2_r1: D8.2, S8.2
c2_r2: D5.2, S5.2
c2_r3: D2.2, S2.2
c2_rt: D11.2, S11.2
c3_r1: D9.2, S9.2
c3_r2: D6.2, S6.2
c3_r3: D3.2, S3.2
c3_rt: D12.2, S12.2
di_c1_r1: LED7.4, LED7.44
di_c1_r2: LED4.4, LED4.44
di_c1_r3: LED1.4, LED1.44
di_c1_rt: LED10.4, LED10.44
di_c2_r1: LED8.4, LED8.44
di_c2_r2: LED5.4, LED5.44
di_c2_r3: LED2.4, LED2.44
di_c2_rt: LED11.4, LED11.44
di_c3_r1: LED9.4, LED9.44
di_c3_r2: LED6.4, LED6.44
di_c3_r3: LED3.4, LED3.44, MCU1.23
di_c3_rt: LED12.4, LED12.44
do_c1_r1: LED7.2, LED7.22
do_c1_r2: LED4.2, LED4.22
do_c1_r3: LED1.2, LED1.22
do_c1_rt: LED10.2, LED10.22
do_c2_r1: LED8.2, LED8.22
do_c2_r2: LED5.2, LED5.22
do_c2_r3: LED2.2, LED2.22
do_c2_rt: LED11.2, LED11.22
do_c3_r1: LED9.2, LED9.22
do_c3_r2: LED6.2, LED6.22
do_c3_r3: LED3.2, LED3.22
do_c3_rt: LED12.2, LED12.22, MCU1.24
